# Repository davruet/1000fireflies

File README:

The Kuramoto Model (1000 Fireflies)
==================================

http://1000fireflies.net

The Kuramoto Model is a Public art event that recruits cyclists and deploys masses of custom bike lights that communicate and synchronize their blinks with one another.

This is a community-based public art project that uses custom-made bike lights to create an interactive event on the scale of a city. LED lights designed and made by Chicago-based artist David Rueter are outfitted with electronics that allow them to communicate with others of their kind and automatically synchronize their blinks, forming a self-organizing system. Individually, these devices appear similar to conventional cycling safety lights, but in groups, they exhibit an immediately noticeable and striking phenomenon of unified flashing.

This September, the project received an Honorary Mention in Interactive Art for the Prix Ars Electronica in Linz, Austria. In 2012, NorthernLights.mn presented The Kuramoto Model in Minneapolis as part of the Northern Spark all-night arts festival.

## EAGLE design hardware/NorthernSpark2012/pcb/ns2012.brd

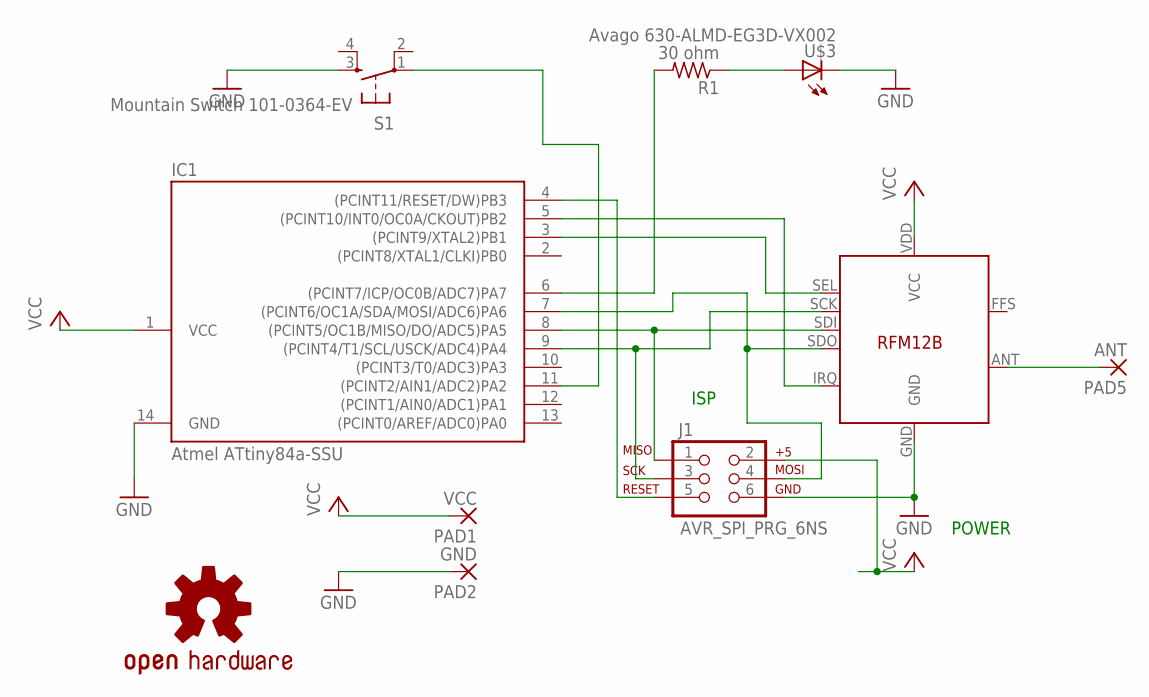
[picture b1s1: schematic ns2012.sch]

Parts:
IC1: Atmel ATtiny84a-SSU; SOIC14
J1: AVR_SPI_PRG_6NS; 2X3-NS
PAD1: VCC; 2,15/1,0
PAD2: GND; 2,15/1,0
PAD5: ANT; 2,15/1,0
R1: 30 ohm; R0805
RFM12B: HopeRF RFM12B-433S1; RFM12B-NARROW
S1: Mountain Switch 101-0364-EV; DTSM-6
U$1: OSHW-LOGOS; OSHW-LOGO-S
U$3: Avago 630-ALMD-EG3D-VX002; ALMD-**3D

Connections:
GND: IC1.14 (GND), J1.6, PAD2.1, RFM12B.GND, S1.3, U$3.C1 (C), U$3.C2 (C)
unnamed: R1.1, U$3.A1 (A), U$3.A2 (A)
unnamed: IC1.9 ((PCINT4/T1/SCL/USCK/ADC4)PA4), J1.3, RFM12B.SCK
unnamed: IC1.8 ((PCINT5/OC1B/MISO/DO/ADC5)PA5), J1.1, RFM12B.SDI
unnamed: IC1.7 ((PCINT6/OC1A/SDA/MOSI/ADC6)PA6), J1.4, RFM12B.SDO
unnamed: IC1.3 ((PCINT9/XTAL2)PB1), RFM12B.SEL
unnamed: IC1.6 ((PCINT7/ICP/OC0B/ADC7)PA7), R1.2
unnamed: IC1.5 ((PCINT10/INT0/OC0A/CKOUT)PB2), RFM12B.IRQ
unnamed: PAD5.1, RFM12B.ANT
unnamed: IC1.11 ((PCINT2/AIN1/ADC2)PA2), S1.1
unnamed: IC1.4 ((PCINT11/RESET/DW)PB3), J1.5
VCC: IC1.1 (VCC), J1.2, PAD1.1, RFM12B.VDD (VCC)

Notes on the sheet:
ISP
POWER

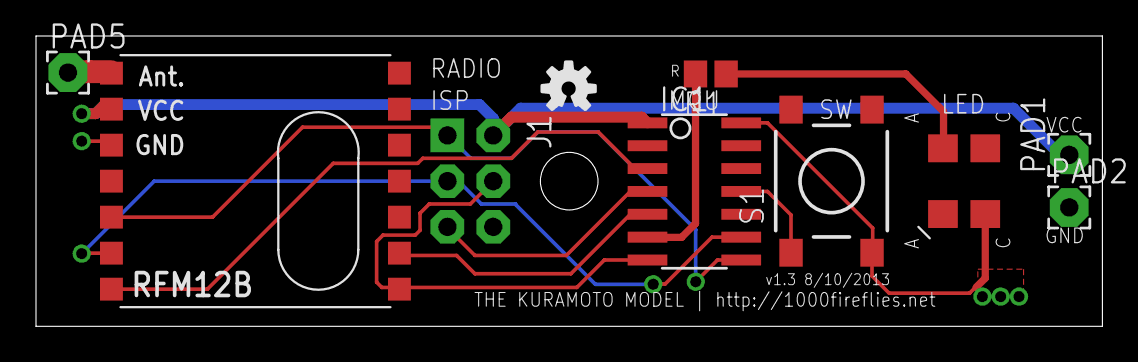
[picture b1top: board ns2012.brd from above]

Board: 2 copper layers, 59.2 x 16.1 mm, 10 parts (0 on the bottom side), 12 nets.

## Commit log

2012-03-23 Added license plus Processing simulation of synchronization algo
2012-04-02 Added basic tumblr theme.
2012-04-02 Added Eagle PCB files, plus gerber output
2012-04-03 Added Kuramoto source
2012-04-03 Added PCI shutdown toggle example code
2012-04-03 Fixed bug with RF12 coms
2012-04-03 Integrated power button code
2012-04-05 Added first rev of box. TODO - enlarge size for 1.4" PCB
2012-04-19 Re-tooled board with 12 mil traces, fewer vias, ground plane, and prettier looks. Moved problematic vias that were too close to pads. Removed unused photoresistor and resistor.
2012-04-19 Memory tweaks, button debouncing, refactoring.
2012-04-19 Added Rhino model for acrylic housing.
2012-04-20 Board redesign, smaller and better vias. Enough room for RFM12B. This rev was submitted to Gold Phoenix PCB for a quote, DARU033475CAQ
2012-05-01 Added startup sequence blinking, shortened cycle time, added reboot on radio failure
2012-05-15 Period now adjusts as well as phase. Changed startup sequence, added shutdown blink as well.
2012-05-15 Added test code.
2012-05-15 Added comment.
2014-08-06 Removed old revisions and added two new ones. General repo cleanup.
2014-08-06 Updated readme.

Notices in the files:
parts and their libraries:
sfe-aesthetics: Licensing: CC v3.0 Share-Alike You are welcome to use this library for commercial purposes.
